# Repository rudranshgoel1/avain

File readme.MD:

# Avain

### Why did I make it?
No specific reason tbh. But, another keyboard I made ([Clavis](https://github.com/rudranshgoel1/clavis)) was a 60%, I lowk wanted an 80% keyboard so I made it.

### What was the hardest part about this ?
Hardest part was actually finding time to make this.

Features:

- RotaryEncoder for Volume Control
- 87 keys (Base + Fn keys + arrow keys + 6 extra keys for home/pg up down and other)
- Raspberry Pi Pico
- Customised layout
- KMK firmware
- Avain Branded PCB
- Custom case

### Schematic

### PCB 

### Case

- Side

I made some aesthetic for Avain. Like I have added holes on all the sides to make it look more good

### 3D view of all parts 

link to full 3d thing-
https://cad.onshape.com/documents/6774359217ff8c97b90facb7/w/2137304fb52ca582983570b9/e/130904d3ca2552892ee4c097?renderMode=0&uiState=69ea524ad3ddea9c2c06a244

A special thanks to Anay and Aditya ( once again ) who are helping me still to make my projects better. Love them so much!

|Name                                                         |Purpose                         |Quantity|Total Cost (INR)|Total Cost (USD)|Link                                                                             |Distributor   |
|-------------------------------------------------------------|--------------------------------|--------|----------------|----------------|---------------------------------------------------------------------------------|--------------|
|Akko Creamy Cyan Switch                                      |Switches for the keyboard       |87      |₹2,598.00       |$28.06          |https://stackskb.com/store/akko-creamy-cyan-switch-pack-of-45-pre-order/         |StacksKB      |
|Black Gray Yellow Cherry Doubleshot PBT Keycaps              |Keycaps for the keyboard        |1       |₹1,399.00       |$15.11          |https://curiositycaps.in/products/black-gray-yellow-cherry-doubleshot-pbt-keycaps|Curiosity Caps|
|Durock Smokey Screw-In Stabilizers V2 (4+1 w/ 6.25u spacebar)|Stabilizers for longer keys     |1       |₹1,595.00       |$17.22          |https://stackskb.com/store/durock-smokey-screw-in-stabilizers-v2/                |StacksKB      |
|EC11 10K Rotary Encoder                                      |RotaryEncoder for Volume Control|1       |N/A             |N/A             |Self Sourced                                                                     |Amazon        |
|Raspberry Pi Pico                                            |MCU for the keyboard            |1       |₹859.00         |$9.01           |https://www.amazon.in/gp/product/B08WPNM7JB                                      |Amazon        |
|1N4148 Diodes                                                |Diodes for the switches         |1       |₹149.00         |$1.61           |https://www.amazon.in/gp/product/B084ZP5BJ3                                      |Amazon        |
|PCB                                                          |Main PCB of the keyboard        |5       |₹3,268.47       |$34.23          |https://jlcpcb.com/                                                              |JLCPCB        |
|Case                                                         |Case for the keyboard           |1       |₹500.00         |$5.40           |Print Legion                                                                     |Print Legion  |
|                                                             |                                |        |                |                |                                                                                 |              |
|                                                             |                                |        |                |                |                                                                                 |              |
|                                                             |                                |        |₹10,368.47      |109.03          |                                                                                 |              |

## Shipping
Amazon + StacksKB = ~$3
Printing Legion = ~$5

Total Shipping = $8

## Total Pricing
The total price comes out to be 10,368.47 INR ($109.03)
Total Shipping = $8

Price After Shipping - 11,175 INR ($117.03)

The pricing might slightly vary due to flash sales, and dollar market trends.

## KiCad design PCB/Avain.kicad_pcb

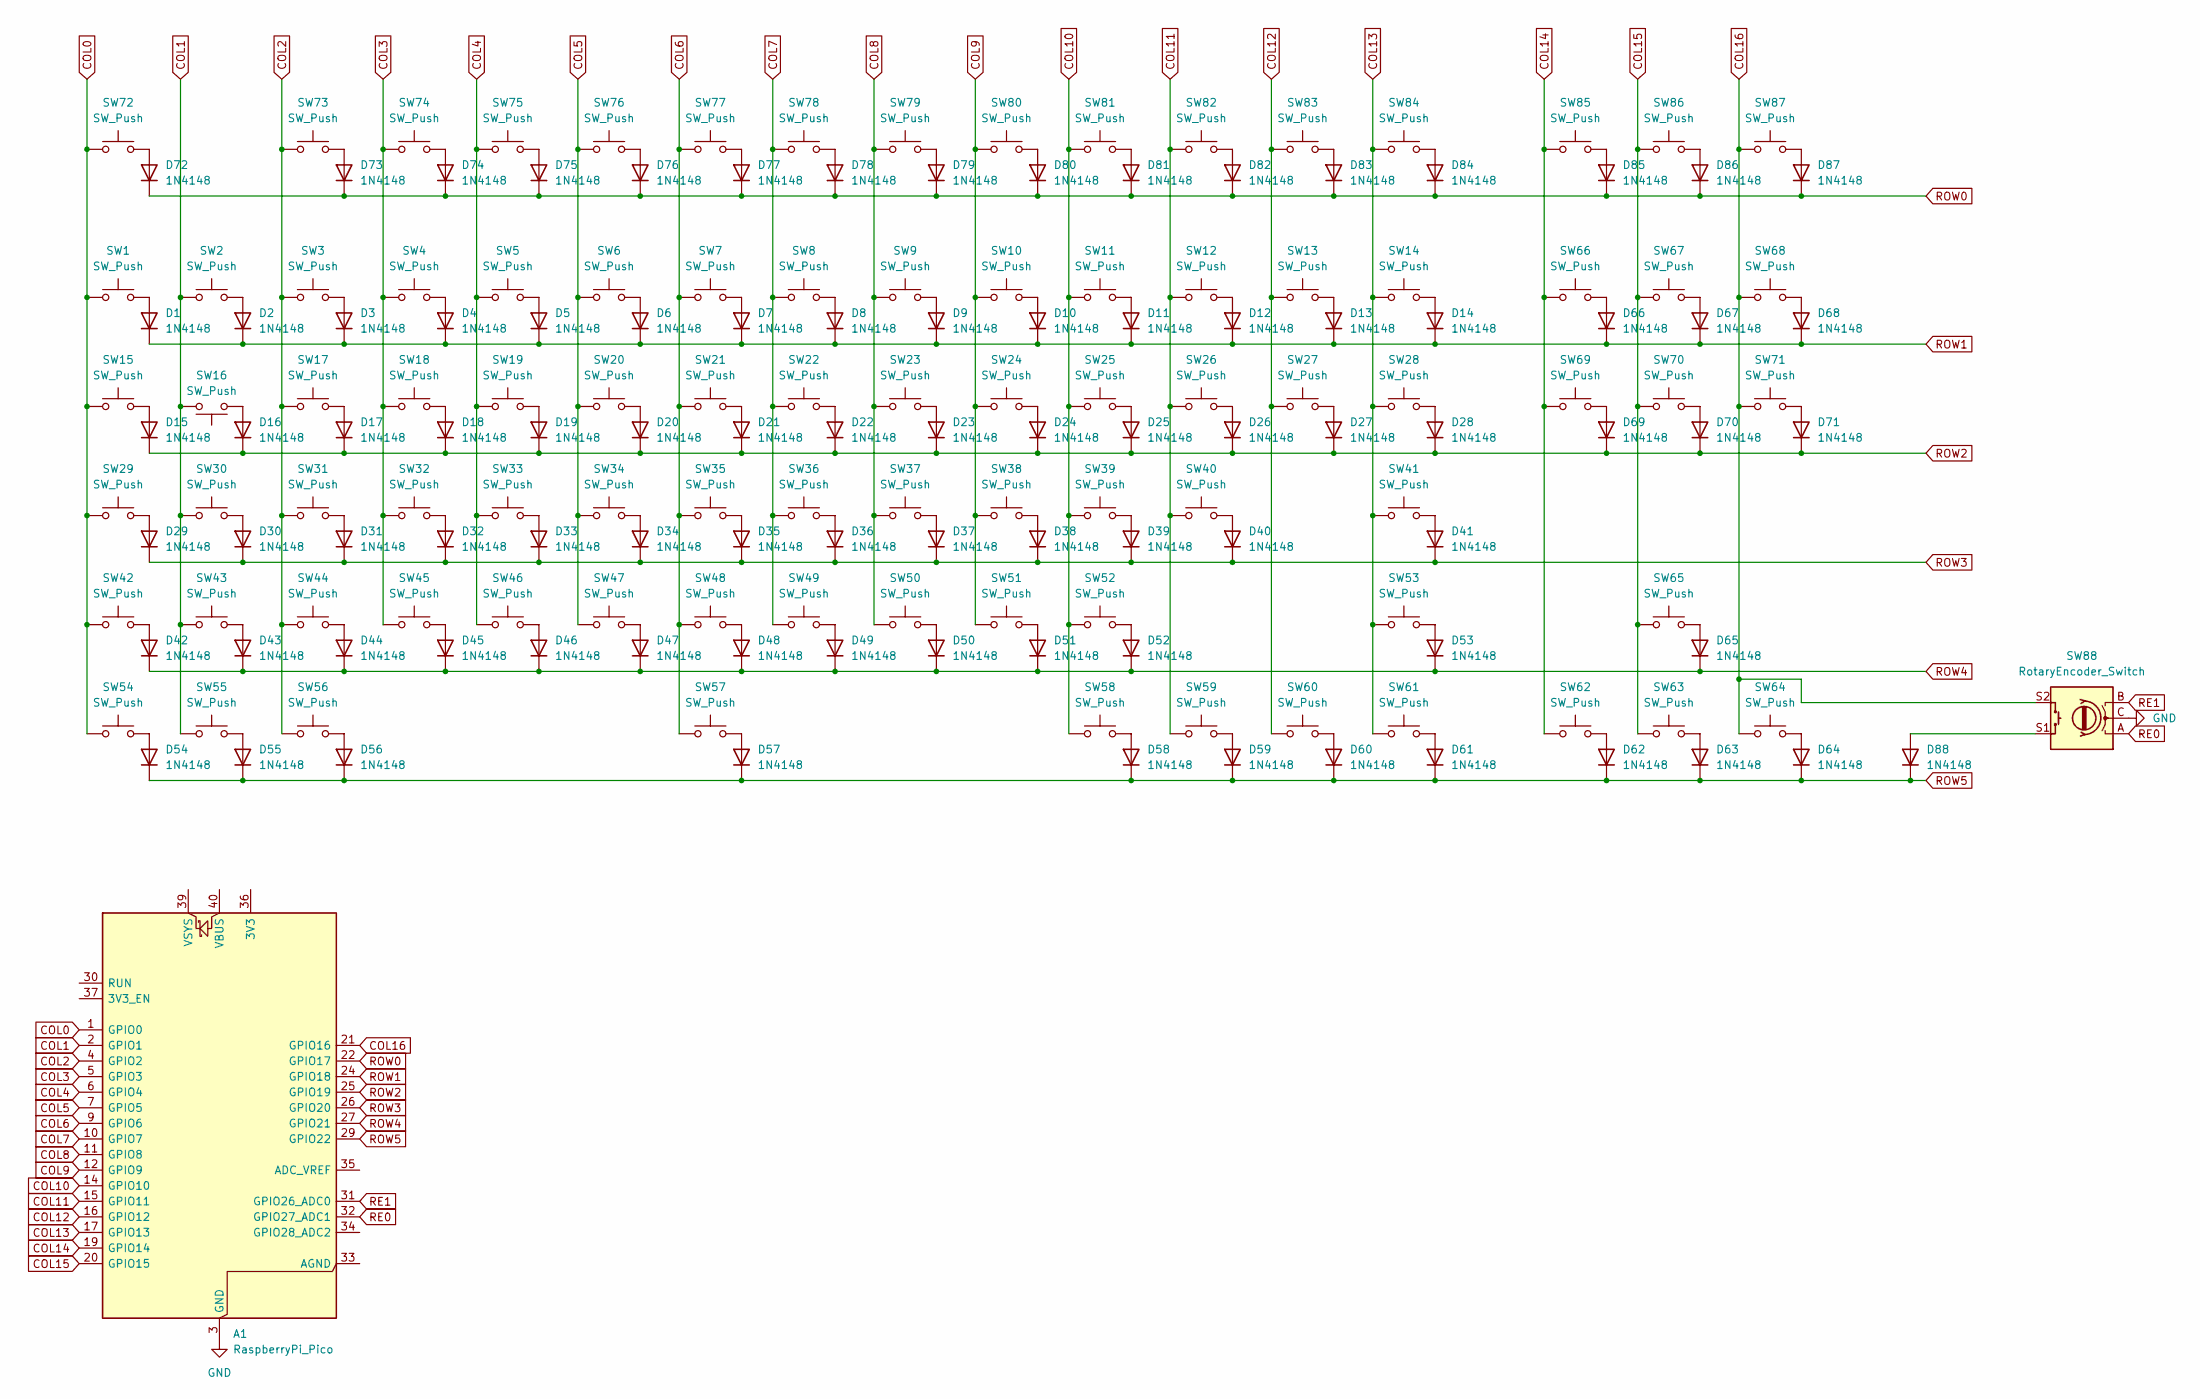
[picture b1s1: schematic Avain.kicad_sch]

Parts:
A1: RaspberryPi_Pico; RaspberryPi_Pico_Common_THT
D1, D2, D3, D4, D5, D6, D7, D8, D9, D10, D11, D12, D13, D14, D15, D16, D17, D18, D19, D20, D21, D22, D23, D24, D25, D26, D27, D28, D29, D30, D31, D32, D33, D34, D35, D36, D37, D38, D39, D40, D41, D42, D43, D44, D45, D46, D47, D48, D49, D50, D51, D52, D53, D54, D55, D56, D57, D58, D59, D60, D61, D62, D63, D64, D65, D66, D67, D68, D69, D70, D71, D72, D73, D74, D75, D76, D77, D78, D79, D80, D81, D82, D83, D84, D85, D86, D87, D88: 1N4148; D_DO-35_SOD27_P7.62mm_Horizontal
SW1, SW2, SW3, SW4, SW5, SW6, SW7, SW8, SW9, SW10, SW11, SW12, SW13, SW16, SW17, SW18, SW19, SW20, SW21, SW22, SW23, SW24, SW25, SW26, SW27, SW30, SW31, SW32, SW33, SW34, SW35, SW36, SW37, SW38, SW39, SW40, SW43, SW44, SW45, SW46, SW47, SW48, SW49, SW50, SW51, SW52, SW62, SW63, SW64, SW65, SW66, SW67, SW68, SW69, SW70, SW71, SW72, SW73, SW74, SW75, SW76, SW77, SW78, SW79, SW80, SW81, SW82, SW83, SW84, SW85, SW86, SW87: SW_Push; SW_Cherry_MX_1.00u_PCB
SW14: SW_Push; SW_Cherry_MX_2.00u_PCB
SW15, SW28: SW_Push; SW_Cherry_MX_1.50u_PCB
SW29: SW_Push; SW_Cherry_MX_1.75u_PCB
SW41, SW42: SW_Push; SW_Cherry_MX_2.25u_PCB
SW53: SW_Push; SW_Cherry_MX_2.75u_PCB
SW54, SW55, SW56, SW58, SW59, SW60, SW61: SW_Push; SW_Cherry_MX_1.25u_PCB
SW57: SW_Push; SW_Cherry_MX_6.25u_PCB
SW88: RotaryEncoder_Switch; RotaryEncoder_Alps_EC11E-Switch_Vertical_H20mm

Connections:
COL0: A1.1 (GPIO0), SW1.1, SW15.1, SW29.1, SW42.1, SW54.1, SW72.1
COL1: A1.2 (GPIO1), SW2.1, SW16.1, SW30.1, SW43.1, SW55.1
COL2: A1.4 (GPIO2), SW3.1, SW17.1, SW31.1, SW44.1, SW56.1, SW73.1
COL3: A1.5 (GPIO3), SW4.1, SW18.1, SW32.1, SW45.1, SW74.1
COL4: A1.6 (GPIO4), SW5.1, SW19.1, SW33.1, SW46.1, SW75.1
COL5: A1.7 (GPIO5), SW6.1, SW20.1, SW34.1, SW47.1, SW76.1
COL6: A1.9 (GPIO6), SW7.1, SW21.1, SW35.1, SW48.1, SW57.1, SW77.1
COL7: A1.10 (GPIO7), SW8.1, SW22.1, SW36.1, SW49.1, SW78.1
COL8: A1.11 (GPIO8), SW9.1, SW23.1, SW37.1, SW50.1, SW79.1
COL9: A1.12 (GPIO9), SW10.1, SW24.1, SW38.1, SW51.1, SW80.1
COL10: A1.14 (GPIO10), SW11.1, SW25.1, SW39.1, SW52.1, SW58.1, SW81.1
COL11: A1.15 (GPIO11), SW12.1, SW26.1, SW40.1, SW59.1, SW82.1
COL12: A1.16 (GPIO12), SW13.1, SW27.1, SW60.1, SW83.1
COL13: A1.17 (GPIO13), SW14.1, SW28.1, SW41.1, SW53.1, SW61.1, SW84.1
COL14: A1.19 (GPIO14), SW62.1, SW66.1, SW69.1, SW85.1
COL15: A1.20 (GPIO15), SW63.1, SW65.1, SW67.1, SW70.1, SW86.1
COL16: A1.21 (GPIO16), SW64.1, SW68.1, SW71.1, SW87.1, SW88.S2
GND: A1.3 (GND), A1.8 (GND), A1.13 (GND), A1.18 (GND), A1.23 (GND), A1.28 (GND), A1.38 (GND), SW88.C
unnamed: D1.2 (A), SW1.2
unnamed: D2.2 (A), SW2.2
unnamed: D3.2 (A), SW3.2
unnamed: D4.2 (A), SW4.2
unnamed: D5.2 (A), SW5.2
unnamed: D6.2 (A), SW6.2
unnamed: D7.2 (A), SW7.2
unnamed: D8.2 (A), SW8.2
unnamed: D9.2 (A), SW9.2
unnamed: D10.2 (A), SW10.2
unnamed: D11.2 (A), SW11.2
unnamed: D12.2 (A), SW12.2
unnamed: D13.2 (A), SW13.2
unnamed: D14.2 (A), SW14.2
unnamed: D15.2 (A), SW15.2
unnamed: D16.2 (A), SW16.2
unnamed: D17.2 (A), SW17.2
unnamed: D18.2 (A), SW18.2
unnamed: D19.2 (A), SW19.2
unnamed: D20.2 (A), SW20.2
unnamed: D21.2 (A), SW21.2
unnamed: D22.2 (A), SW22.2
unnamed: D23.2 (A), SW23.2
unnamed: D24.2 (A), SW24.2
unnamed: D25.2 (A), SW25.2
unnamed: D26.2 (A), SW26.2
unnamed: D27.2 (A), SW27.2
unnamed: D28.2 (A), SW28.2
unnamed: D29.2 (A), SW29.2
unnamed: D30.2 (A), SW30.2
unnamed: D31.2 (A), SW31.2
unnamed: D32.2 (A), SW32.2
unnamed: D33.2 (A), SW33.2
unnamed: D34.2 (A), SW34.2
unnamed: D35.2 (A), SW35.2
unnamed: D36.2 (A), SW36.2
unnamed: D37.2 (A), SW37.2
unnamed: D38.2 (A), SW38.2
unnamed: D39.2 (A), SW39.2
unnamed: D40.2 (A), SW40.2
unnamed: D41.2 (A), SW41.2
unnamed: D42.2 (A), SW42.2
unnamed: D43.2 (A), SW43.2
unnamed: D44.2 (A), SW44.2
unnamed: D45.2 (A), SW45.2
unnamed: D46.2 (A), SW46.2
unnamed: D47.2 (A), SW47.2
unnamed: D48.2 (A), SW48.2
unnamed: D49.2 (A), SW49.2
unnamed: D50.2 (A), SW50.2
unnamed: D51.2 (A), SW51.2
unnamed: D52.2 (A), SW52.2
unnamed: D53.2 (A), SW53.2
unnamed: D54.2 (A), SW54.2
unnamed: D55.2 (A), SW55.2
unnamed: D56.2 (A), SW56.2
unnamed: D57.2 (A), SW57.2
unnamed: D58.2 (A), SW58.2
unnamed: D59.2 (A), SW59.2
unnamed: D60.2 (A), SW60.2
unnamed: D61.2 (A), SW61.2
unnamed: D62.2 (A), SW62.2
unnamed: D63.2 (A), SW63.2
unnamed: D64.2 (A), SW64.2
unnamed: D65.2 (A), SW65.2
unnamed: D66.2 (A), SW66.2
unnamed: D67.2 (A), SW67.2
unnamed: D68.2 (A), SW68.2
unnamed: D69.2 (A), SW69.2
unnamed: D70.2 (A), SW70.2
unnamed: D71.2 (A), SW71.2
unnamed: D72.2 (A), SW72.2
unnamed: D73.2 (A), SW73.2
unnamed: D74.2 (A), SW74.2
unnamed: D75.2 (A), SW75.2
unnamed: D76.2 (A), SW76.2
unnamed: D77.2 (A), SW77.2
unnamed: D78.2 (A), SW78.2
unnamed: D79.2 (A), SW79.2
unnamed: D80.2 (A), SW80.2
unnamed: D81.2 (A), SW81.2
unnamed: D82.2 (A), SW82.2
unnamed: D83.2 (A), SW83.2
unnamed: D84.2 (A), SW84.2
unnamed: D85.2 (A), SW85.2
unnamed: D86.2 (A), SW86.2
unnamed: D87.2 (A), SW87.2
unnamed: D88.2 (A), SW88.S1
RE0: A1.32 (GPIO27_ADC1), SW88.A
RE1: A1.31 (GPIO26_ADC0), SW88.B
ROW0: A1.22 (GPIO17), D72.1 (K), D73.1 (K), D74.1 (K), D75.1 (K), D76.1 (K), D77.1 (K), D78.1 (K), D79.1 (K), D80.1 (K), D81.1 (K), D82.1 (K), D83.1 (K), D84.1 (K), D85.1 (K), D86.1 (K), D87.1 (K)
ROW1: A1.24 (GPIO18), D1.1 (K), D2.1 (K), D3.1 (K), D4.1 (K), D5.1 (K), D6.1 (K), D7.1 (K), D8.1 (K), D9.1 (K), D10.1 (K), D11.1 (K), D12.1 (K), D13.1 (K), D14.1 (K), D66.1 (K), D67.1 (K), D68.1 (K)
ROW2: A1.25 (GPIO19), D15.1 (K), D16.1 (K), D17.1 (K), D18.1 (K), D19.1 (K), D20.1 (K), D21.1 (K), D22.1 (K), D23.1 (K), D24.1 (K), D25.1 (K), D26.1 (K), D27.1 (K), D28.1 (K), D69.1 (K), D70.1 (K), D71.1 (K)
ROW3: A1.26 (GPIO20), D29.1 (K), D30.1 (K), D31.1 (K), D32.1 (K), D33.1 (K), D34.1 (K), D35.1 (K), D36.1 (K), D37.1 (K), D38.1 (K), D39.1 (K), D40.1 (K), D41.1 (K)
ROW4: A1.27 (GPIO21), D42.1 (K), D43.1 (K), D44.1 (K), D45.1 (K), D46.1 (K), D47.1 (K), D48.1 (K), D49.1 (K), D50.1 (K), D51.1 (K), D52.1 (K), D53.1 (K), D65.1 (K)
ROW5: A1.29 (GPIO22), D54.1 (K), D55.1 (K), D56.1 (K), D57.1 (K), D58.1 (K), D59.1 (K), D60.1 (K), D61.1 (K), D62.1 (K), D63.1 (K), D64.1 (K), D88.1 (K)

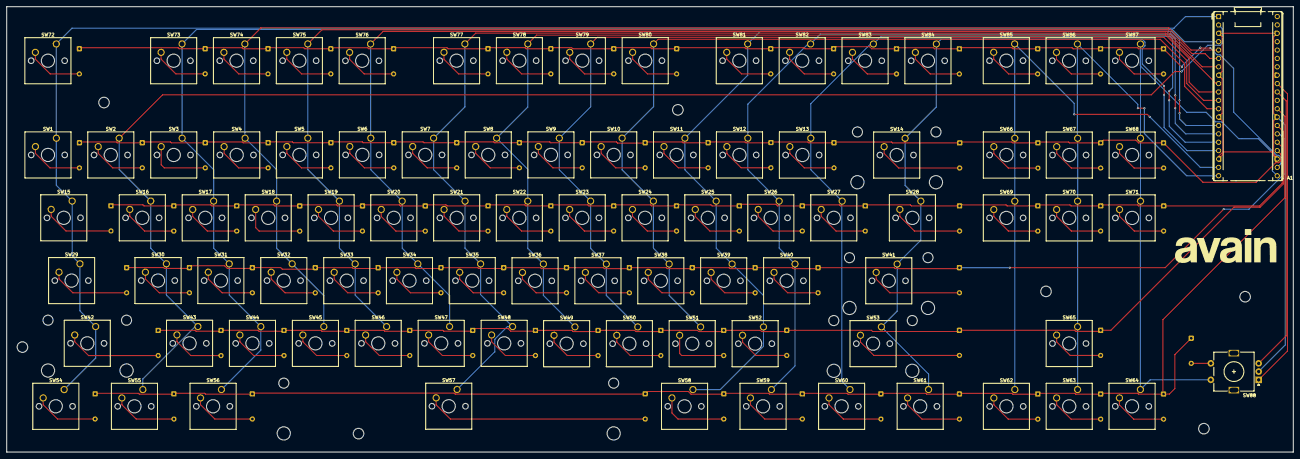
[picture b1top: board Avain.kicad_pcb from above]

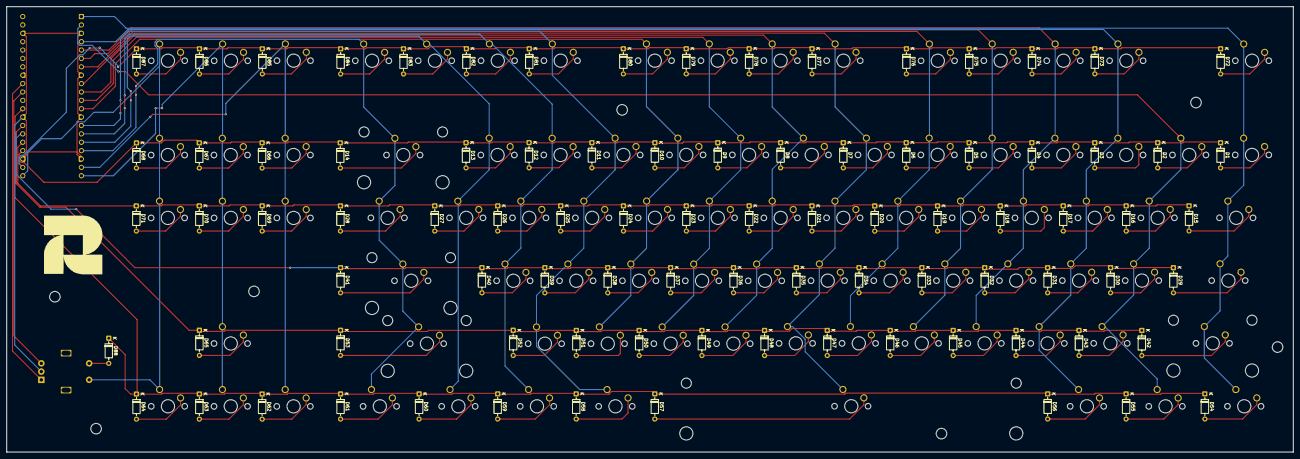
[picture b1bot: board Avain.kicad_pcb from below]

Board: 2 copper layers, 390.0 x 135.0 mm, 177 parts (88 on the bottom side), 114 nets.

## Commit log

2026-04-12 main commit
2026-04-12 fix BOM
2026-04-12 added images
2026-04-23 updated bom
2026-04-23 final commit, ready to ship
2026-04-26 last minute bom update
2026-06-16 added case files
